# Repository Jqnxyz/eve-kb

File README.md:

# Eve

Tiny keyboard thing. Unsure of it's own purpose (yet)

## License

Shield: [![CC BY-SA 4.0][cc-by-sa-shield]][cc-by-sa]

This work is licensed under a
[Creative Commons Attribution-ShareAlike 4.0 International License][cc-by-sa].

[![CC BY-SA 4.0][cc-by-sa-image]][cc-by-sa]

[cc-by-sa]: http://creativecommons.org/licenses/by-sa/4.0/
[cc-by-sa-image]: https://licensebuttons.net/l/by-sa/4.0/88x31.png
[cc-by-sa-shield]: https://img.shields.io/badge/License-CC%20BY--SA%204.0-lightgrey.svg

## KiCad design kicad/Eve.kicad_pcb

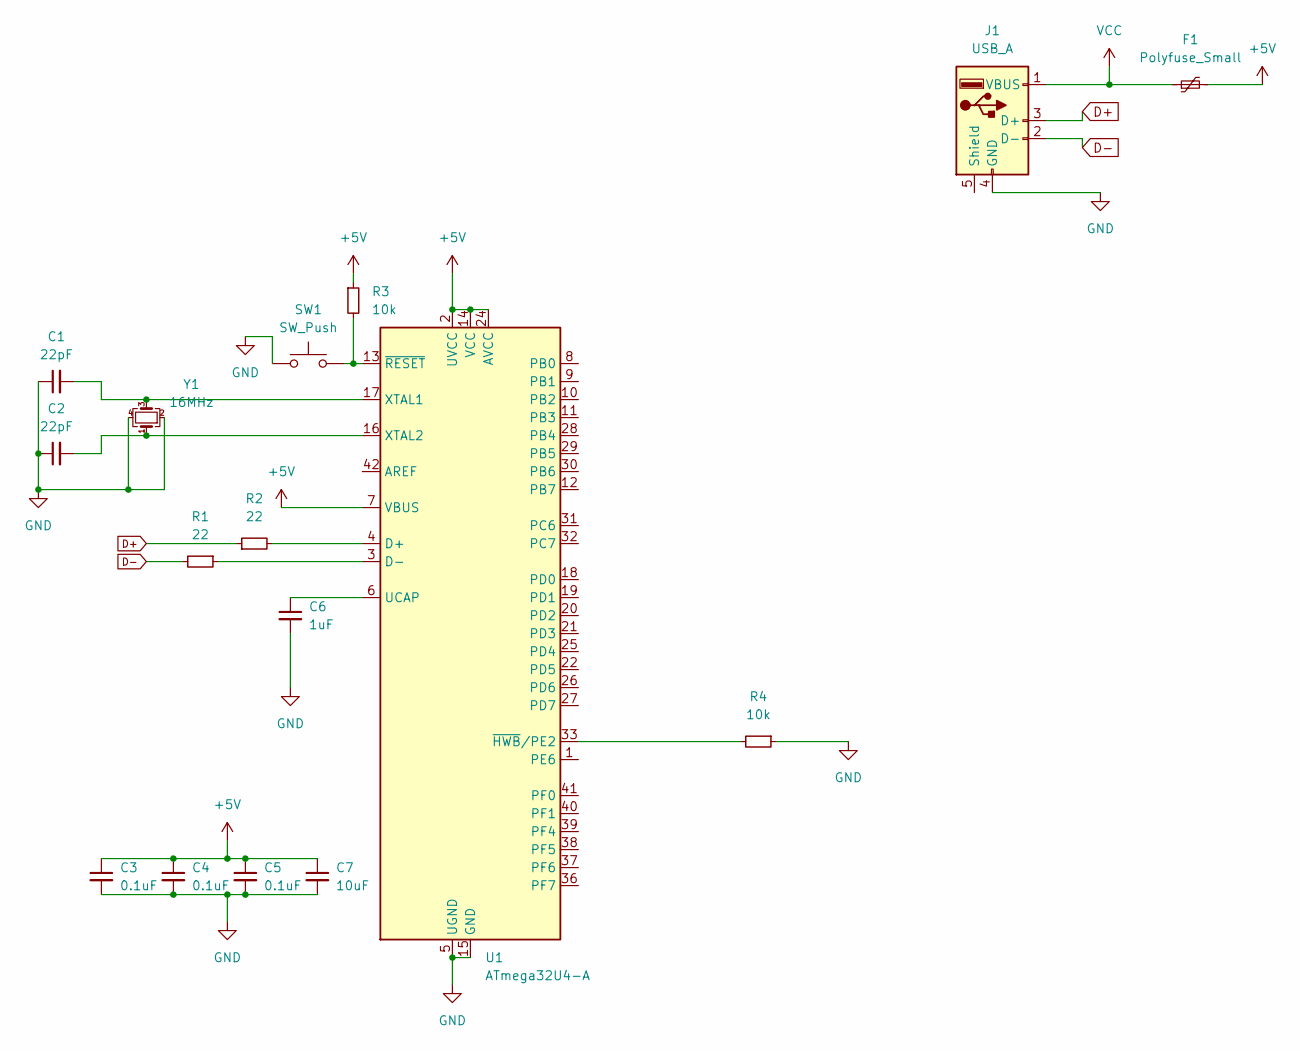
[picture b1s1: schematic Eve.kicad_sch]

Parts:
C1, C2: 22pF; C_0805_2012Metric
C3, C4, C5: 0.1uF; C_0805_2012Metric
C6: 1uF; C_0805_2012Metric
C7: 10uF; C_0805_2012Metric
F1: Polyfuse_Small; Fuse_1206_3216Metric
J1: USB_A; USB_Micro-B_Molex-105017-0001
R1, R2: 22; R_0805_2012Metric
R3, R4: 10k; R_0805_2012Metric
SW1: SW_Push; SKQG-1155865
U1: ATmega32U4-A; TQFP-44_10x10mm_P0.8mm
Y1: 16MHz; Crystal_SMD_3225-4Pin_3.2x2.5mm

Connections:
+5V: C3.1, C4.1, C5.1, C7.1, F1.2, R3.1, U1.2 (UVCC), U1.7 (VBUS), U1.14 (VCC), U1.24 (AVCC), U1.34 (VCC), U1.44 (AVCC)
D+: J1.3 (D+), R2.1
D-: J1.2 (D-), R1.2
GND: C1.1, C2.1, C3.2, C4.2, C5.2, C6.2, C7.2, J1.4 (GND), R4.1, SW1.1, U1.5 (UGND), U1.15 (GND), U1.23 (GND), U1.35 (GND), U1.43 (GND), Y1.2, Y1.4
unnamed: C1.2, U1.17 (XTAL1), Y1.3
unnamed: C2.2, U1.16 (XTAL2), Y1.1
unnamed: C6.1, U1.6 (UCAP)
unnamed: R1.1, U1.3 (D-)
unnamed: R2.2, U1.4 (D+)
unnamed: R3.2, SW1.2, U1.13 (~RESET)
unnamed: R4.2, U1.33 (~HWB/PE2)
VCC: F1.1, J1.1 (VBUS)

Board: 2 copper layers, 16 parts (0 on the bottom side), 12 nets, no tracks yet.

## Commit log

2022-05-06 Initial Commit
    Add README and Kicad project
2022-05-06 Add Submodule
2022-05-06 Add MCU and USB schematic
2022-05-06 Assign footprints
2022-05-06 Add basic PCB
2022-05-07 Remove PCB design
    Pivoting project
2022-05-07 Change USB port to USB-C
2022-05-07 Add .gitignore
2022-05-07 Remove temp files
2022-05-07 Remove .DS_Store
2022-05-07 Add labels
